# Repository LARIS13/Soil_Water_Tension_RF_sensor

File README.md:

# Soil_Water_Tension_RF_sensor
Implementation of Watermark sensor using arduino, attiny85 and RF modules including:

C++ code  
KiCad blueprints for PCB  
LaTeX document explaining theory, limitations and implementation of water measurement techniques.

# Dependencies:  
Manchester RF library: https://github.com/mchr3k/arduino-libs-manchester  
tinysnore is only used to sleep Attiny85 for more than the max Watchdog timer time, which is around 8 seconds: https://github.com/connornishijima/TinySnore

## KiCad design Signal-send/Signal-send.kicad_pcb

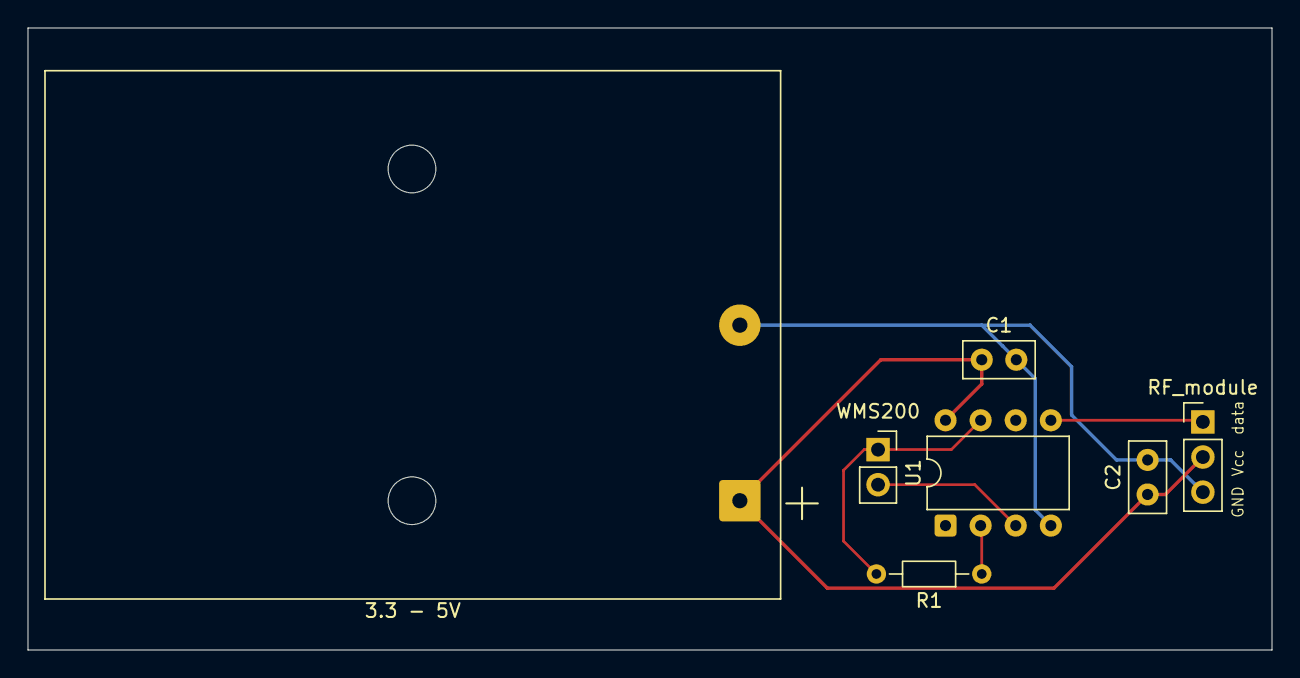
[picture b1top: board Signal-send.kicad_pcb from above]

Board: 2 copper layers, 90.0 x 45.0 mm, 7 parts (0 on the bottom side), 5 nets.

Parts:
3.3 - 5V: BatteryHolder_Keystone_2479_3xAAA
C1: 0.1uF; C_Disc_D5.0mm_W2.5mm_P2.50mm
C2: 100uF; C_Disc_D5.0mm_W2.5mm_P2.50mm
R1: 10k; R_Axial_DIN0204_L3.6mm_D1.6mm_P7.62mm_Horizontal
RF_module: PinHeader_1x03_P2.54mm_Vertical
U1: ATtiny85V-10P; DIP-8_W7.62mm
WMS200: WMS200; PinSocket_1x02_P2.54mm_Vertical

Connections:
+5V: 3.3 - 5V.1, C1.1, C2.1, RF_module.2, U1.8 (VCC)
GNDREF: 3.3 - 5V.2, C1.2, C2.2, RF_module.3, U1.4 (GND)
unnamed: R1.2, U1.7 (PB2), WMS200.1
unnamed: R1.1, U1.2 (XTAL1/PB3)
unnamed: U1.3 (XTAL2/PB4), WMS200.2

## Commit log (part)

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2026-02-01 Added KiCad files of sending circuit
2026-03-02 Enhance README with more project details
    Expanded project description to include additional resources and documentation.
2026-03-02 Fix formatting in README.md for consistency
2026-03-02 Added code for Reciever and Transmitter, aswell as examples for math regarding sensor reading
2026-03-02 Add dependencies section to README
    Added dependencies section with relevant links.
2026-05-13 Added files of SWT_TX_V1
    also added gerbers of V1
2026-05-13 updated to working version of rx
    Buffer size change.
    Array of 4 u8ints. 0 is size of message, 1 is A1, 2 is A2 and 3 is Tx from which the message comes from.
2026-05-13 Updated to working version of TX
    can only send arrays with all elements of same type due to memory addressing used in library.
